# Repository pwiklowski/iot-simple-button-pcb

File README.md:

## Schematic

## PCB

## PCB (missing power supply elements)

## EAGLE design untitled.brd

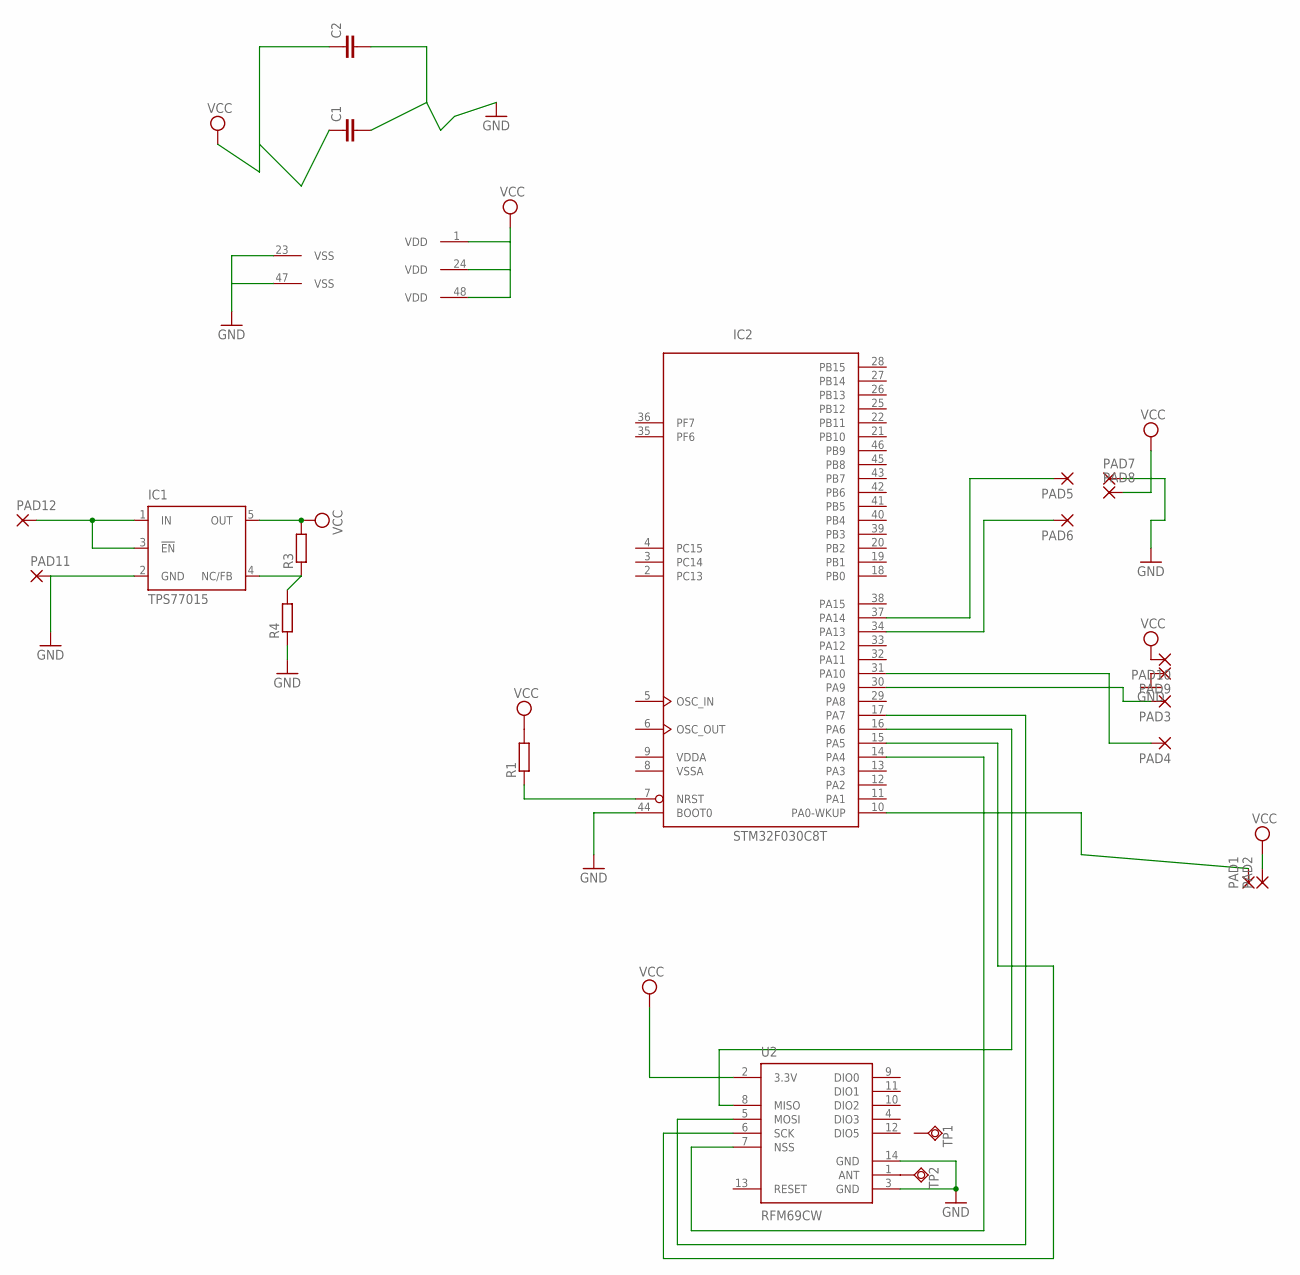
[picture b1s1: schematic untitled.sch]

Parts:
C1, C2: C-EUC1206; C1206
IC1: TPS77015; SOT23-DBV
IC2: STM32F030C8T; LQFP48
PAD1, PAD2, PAD3, PAD4, PAD5, PAD6, PAD7, PAD8, PAD9, PAD10, PAD11, PAD12: SMD2; SMD1,27-2,54
R1: R-EU_M1206; M1206
R3, R4: R-EU_M0805; M0805
TP1, TP2: TPSQTP20SQ; TP20SQ
U2: RFM69CW; RFM69CW-XXXS2

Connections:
GND: C1.2, C2.2, IC1.2 (GND), IC2.23 (VSS), IC2.44 (BOOT0), IC2.47 (VSS), PAD7.1, PAD9.1, PAD11.1, R4.1, U2.3 (GND), U2.14 (GND)
unnamed: IC2.7 (NRST), R1.1
unnamed: IC2.37 (PA14), PAD5.1
unnamed: IC2.16 (PA6), U2.8 (MISO)
unnamed: IC2.14 (PA4), U2.7 (NSS)
unnamed: TP2.TP, U2.1 (ANT)
unnamed: IC2.17 (PA7), U2.5 (MOSI)
unnamed: IC2.34 (PA13), PAD6.1
unnamed: IC2.30 (PA9), PAD3.1
unnamed: IC2.31 (PA10), PAD4.1
unnamed: IC2.10 (PA0-WKUP), PAD1.1
unnamed: IC1.1 (IN), IC1.3 (!EN), PAD12.1
unnamed: IC2.15 (PA5), U2.6 (SCK)
unnamed: IC1.4 (NC/FB), R3.1, R4.2
VCC: C1.1, C2.1, IC1.5 (OUT), IC2.1 (VDD), IC2.24 (VDD), IC2.48 (VDD), PAD2.1, PAD8.1, PAD10.1, R1.2, R3.2, U2.2 (3.3V)
VDDA: IC2.9 (VDDA)
VSSA: IC2.8 (VSSA)

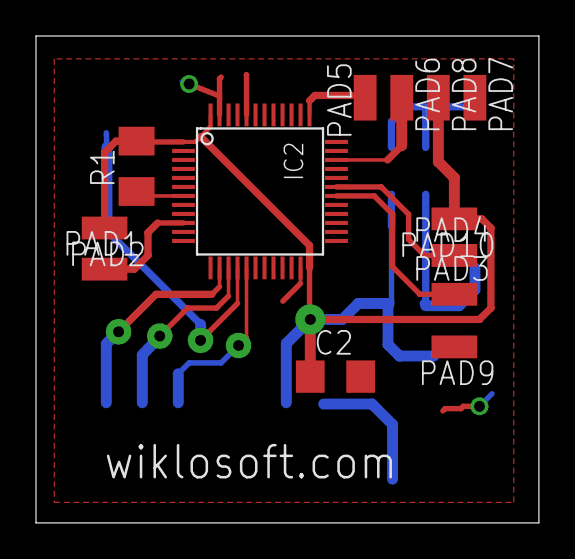
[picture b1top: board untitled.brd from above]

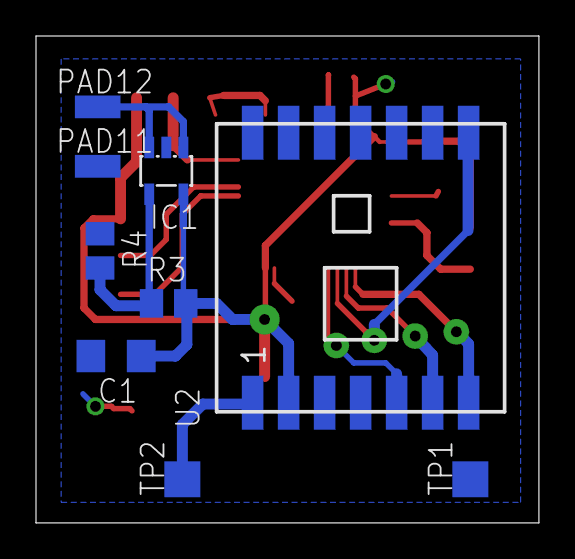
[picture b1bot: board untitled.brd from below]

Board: 2 copper layers, 27.9 x 27.1 mm, 22 parts (9 on the bottom side), 15 nets.

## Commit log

2016-08-04 version 0.1
2016-08-04 version 0.2
2016-08-05 version 0.3 - proto 1
2016-08-21 Change MCU to bigger version
2016-08-24 Fix jtag pins
2016-11-22 Fix usasrt/i2c pins
2016-11-22 add readme
